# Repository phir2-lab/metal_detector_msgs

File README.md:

# Open Hardware, ROS-enable metal detector

This is a ROS package for the metal detector used in the [HRATC2017](http://inf.ufrgs.br/hratc2017/HRATC2017/Welcome.html) robot programming competition. The detector is based on open-hardware and software design.

## Usage

Program your Arduino with the firmware located in the "electronics/arduino_firmware" folder, connect it to your computer and run the launch file "detector.launch" with:

```
roslaunch metal_detector_msgs detector.launch
```

Or run the "arduino_node.py" node with:

```
rosrun metal_detector_msgs arduino_node.py [args]
```

The arguments (optional) to be passed to the node are:
* -b, --baud : Serial BAUD rate of the Arduino (default is 9600)
* --vid 	 : Vendor ID of the Arduino (default is 2341 for Arduino UNO)

This can also be seen when passing "-h" as argument for the node.

## Dependencies
* [ROS Indigo](http://wiki.ros.org/indigo)
* [pySerial](http://pyserial.readthedocs.io/en/latest/pyserial.html)

## Installation

Clone this package to your [Catkin Workspace](http://wiki.ros.org/catkin/Tutorials/create_a_workspace) "src" folder and [build your catkin packages](http://wiki.ros.org/catkin/Tutorials/using_a_workspace).

## Topic

The node receives frequency measurements from an Arduino via Serial Communication and publishes a topic of the Coil message type, of which the definition can be seen in the "msg" folder. Please see the readme of the "msg" folder for more information regarding interface with the coils.

## Parameters

The package uses ROS' parameter server to get and set its calibration parameters. They are defined as:

* calibration/sat : Saturation value for the coils in Hz
* calibration/ref : The desired reference value (when coils saturate)

By default, these parameters are set to "1.0".
The node also caps the readings to the reference value. In other words, it returns readings in the range of [0 - ref].

The parameters can be set statically via the "detector.launch" file. Just change the <param> tags accordingly, as seen in the example below:

```
<param name="calibration/sat" type="double" value="1853" /> 
```

Alternatively, to set the parameters dynamically, use the command below after launching the detector node:

```
rosparam set calibration/sat 1853
```

To check the value of a parameter, use the "rosparam get" command:
```
rosparam get calibration/sat
```

## Package organization

- model: has the Solidworks and Gazebo models for the metal detector;
- eletronics: it has the hardware design, eletronics, and Arduino programming;
- other dirs: ROS-related files such as launch, node, msg, etc.

## Troubleshooting

* Can't connect to my Arduino

The "arduino_node.py" sweeps your /dev/ folder for all available serial connections and finds the Arduino automatically via its Vendor ID (vid). The Arduino's vid can be set through the "--vid" argument when running the node, or by changing the "args" parameter in the launch file. To find out what your Arduino vid is, connect it to a computer and run the "lsusb" command in a terminal. The vid will be there, like this:

<pre>
Bus 002 Device 006: ID 0cf3:e005 Atheros Communications, Inc. 
Bus 002 Device 003: ID 0c45:6712 Microdia 
Bus 002 Device 009: ID <b>2341</b>:0043 Arduino SA Uno R3 (CDC ACM)
                          ^
                       [This is your VID]   
</pre>

## Credits

- The original eletronics board was designed by [LucasLab](https://translate.google.com/translate?sl=auto&tl=en&js=y&prev=_t&hl=pt-BR&ie=UTF-8&u=http%3A%2F%2Fwww.lucaslab.grandhost.pl%2Flucaslab%2Fwykrywacz_PI.htm&edit-text=)
- The integration of the eletronics board with Arduino is by Augusto Bergamin;
- The Arduino firmware is by Augusto Bergamin and Renan Maidana;
- The ROS node design and ROS launch is by Renan Maidana;
- Conversion from SolidWorks to Gazebo by Renan Maffei and Mathias Mantelli.
- Readmes edits by Alexandre Amory.

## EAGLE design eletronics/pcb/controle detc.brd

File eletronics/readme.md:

# Electronics

This directory you will find:

- Arduino Firmware
- original metal detector PCB design [LucasLab](https://translate.google.com/translate?sl=auto&tl=en&js=y&prev=_t&hl=pt-BR&ie=UTF-8&u=http%3A%2F%2Fwww.lucaslab.grandhost.pl%2Flucaslab%2Fwykrywacz_PI.htm&edit-text=)
- modified metal detector PCB design by Augusto Bergamin
  - integrated with Arduino UNO
  - including support to two coils

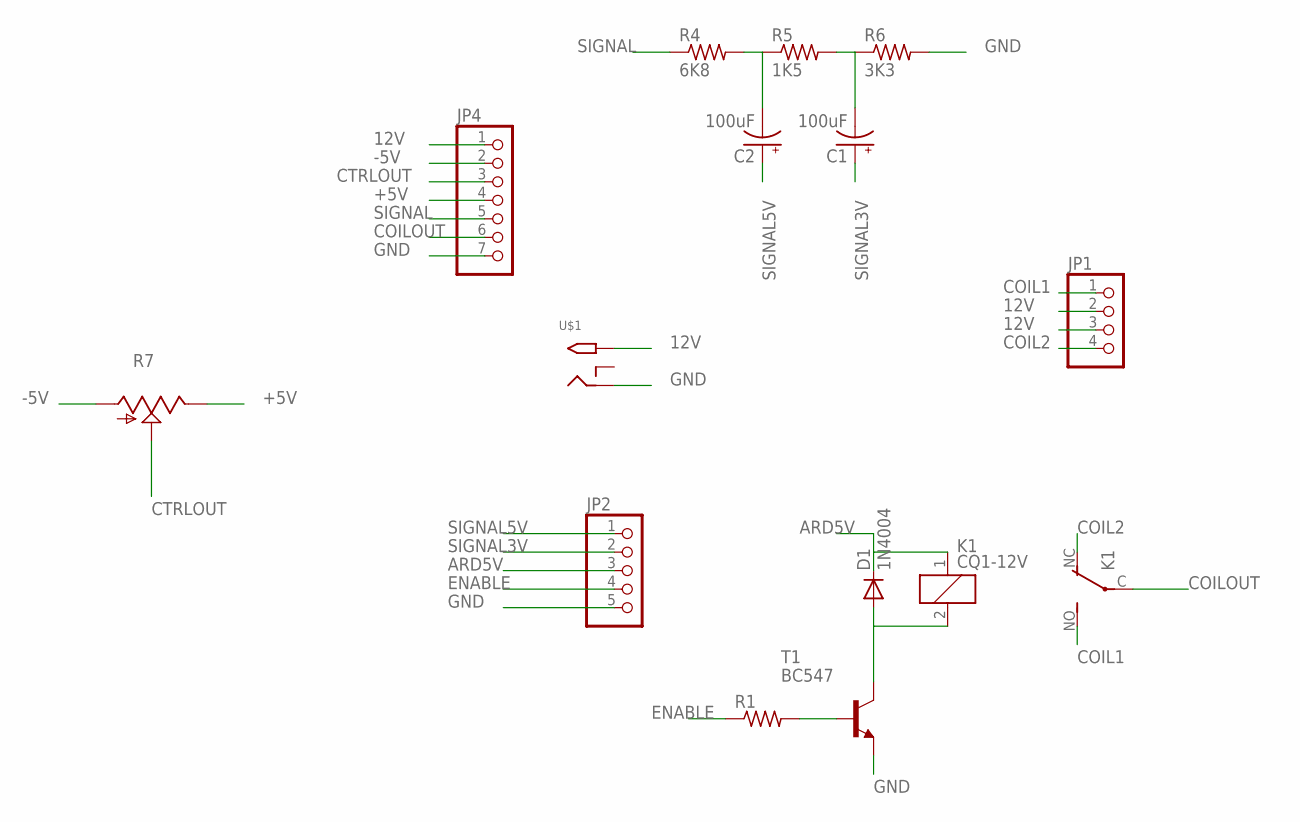
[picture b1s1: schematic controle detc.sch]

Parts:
C1, C2: 100uF; E5-8,5
D1: 1N4004; DO41-10
JP1: PINHD-1X4; 1X04
JP2: PINHD-1X5; 1X05
JP4: PINHD-1X7; 1X07
K1: CQ1-12V; CQ1
R1: R-US_0207/7; 0207/7
R4: 6K8; 0207/7
R5: 1K5; 0207/7
R6: 3K3; 0207/7
R7: TRIM_US-S64W; S64W
T1: BC547; TO92
U$1: 2.1MMJACKTHM; PJ-102A

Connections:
12V: JP1.2, JP1.3, JP4.1, U$1.TIP
+5V: JP4.4, R7.E
-5V: JP4.2, R7.A
ARD5V: D1.C, JP2.3, K1.1
COIL1: JP1.1, K1.NO (S)
COIL2: JP1.4, K1.NC (O)
COILOUT: JP4.6, K1.C
CTRLOUT: JP4.3, R7.S
ENABLE: JP2.4, R1.1
GND: JP2.5, JP4.7, R6.2, T1.1 (E), U$1.RING
unnamed: R1.2, T1.2 (B)
unnamed: D1.A, K1.2, T1.3 (C)
unnamed: C2.-, R4.2, R5.1
unnamed: C1.-, R5.2, R6.1
SIGNAL: JP4.5, R4.1
SIGNAL3V: C1.+, JP2.2
SIGNAL5V: C2.+, JP2.1

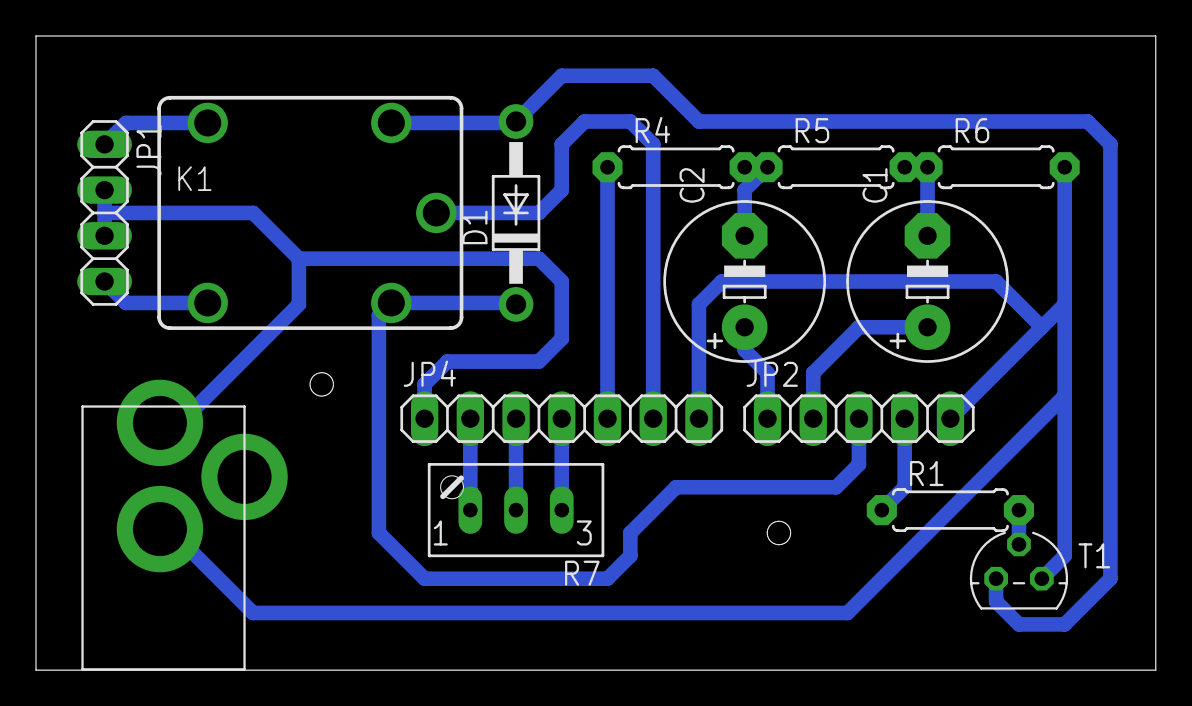
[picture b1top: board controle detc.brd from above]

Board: 2 copper layers, 62.2 x 35.2 mm, 14 parts (0 on the bottom side), 17 nets.

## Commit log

2014-02-27 First commit.
2016-11-08 adding new dir structure for LSA's metal detector
2016-11-08 readme
2016-11-08 Upload metaldetector solidworks files
    SW 2014
2016-11-08 Added metal detector arduino firmware
2016-11-08 Added metal_detector launch and readme
2016-11-09 creating dir to place gazebo models
2016-11-09 Changed 'package.xml' and 'CMakeLists.txt'
2016-11-09 Changed 'detector.launch'
2016-11-09 Adicionado Esquemáticos do detector
2016-11-09 Added Gazebo model of the metal detector
2016-11-10 Update of metal_detector URDF model
2016-11-14 ADD credits to the detectors creator
2016-11-14 google translate
2016-11-18 Corrected syntax bug in detector_firm.ino
2016-11-19 Changed CMakeLists.txt
2016-11-19 Added scripts folder with arduino_node.py file
2016-11-19 Changed detector.launch
2016-11-19 Changed arduino_node.py
2016-11-19 Changed README.md
2016-11-21 Changed detector_firm.ino
2016-11-28 Adicionadas Bobinas Novas
2016-12-05 Modified arduino_node.py
2016-12-05 Changed message type of Coil.msg from int32 to float32
2016-12-05 Added launch parameters for metal detector node
2016-12-05 hanged arduino_node.py
2016-12-05 Updated README.md with parameter descriptions and usage
2016-12-07 Added README.md
2016-12-07 Changed measurement field from channel to left_coil and right_coil
2016-12-07 Changed arduino_node.py to reflect changes in Coil.msg file
2016-12-07 Corrected typos in comments on arduino_node.py
2016-12-07 Changed README.md to reflect changes in Coil.msg
2016-12-09 new metal detector image. editing readmes
2016-12-09 URDF of the metal detector updated
2017-03-11 added bag files and changed arduino firmware
2017-03-16 remove duplicated arduino firmware
2017-03-16 renamed metal detector topic in bags
